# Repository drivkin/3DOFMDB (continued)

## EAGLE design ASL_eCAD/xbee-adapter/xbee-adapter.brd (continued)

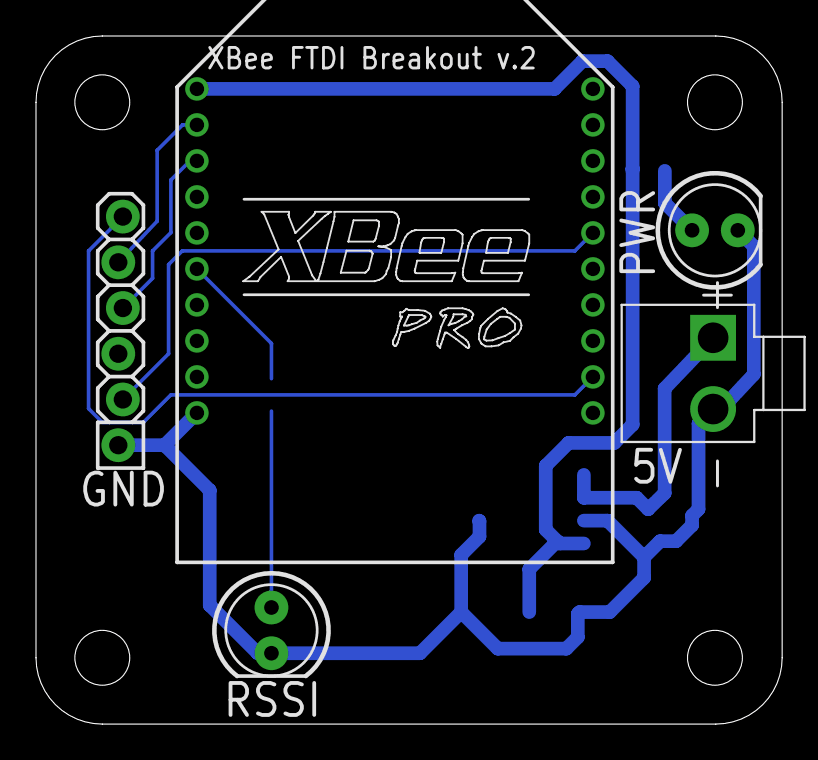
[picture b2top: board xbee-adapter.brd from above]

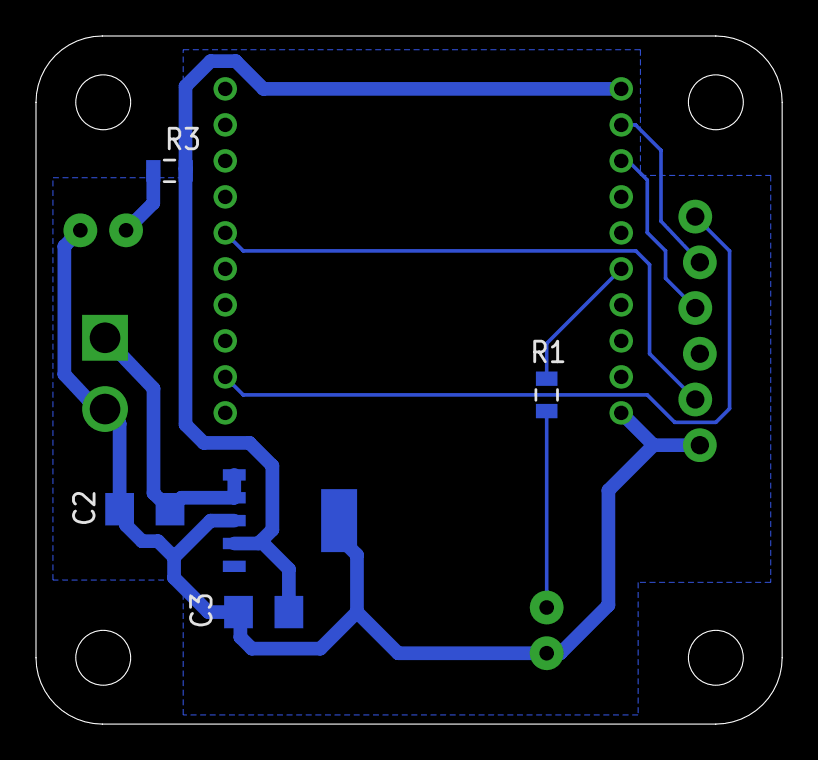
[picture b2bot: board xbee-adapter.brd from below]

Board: 2 copper layers, 41.5 x 38.2 mm, 14 parts (5 on the bottom side), 10 nets.

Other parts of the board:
E$1, E$2, E$3, E$4: STAND-OFF-TIGHT

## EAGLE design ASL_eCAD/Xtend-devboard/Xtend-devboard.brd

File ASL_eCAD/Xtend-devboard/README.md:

# Xtend-devboard

## Description

This board provides a TTL-leve UART connection the Xtend09 wireless modem. The 6-pin header is pinned-out for a standard FTDI cable. This board does not connect power and relies on external power, 2.7-5.5V for the Xtend09.

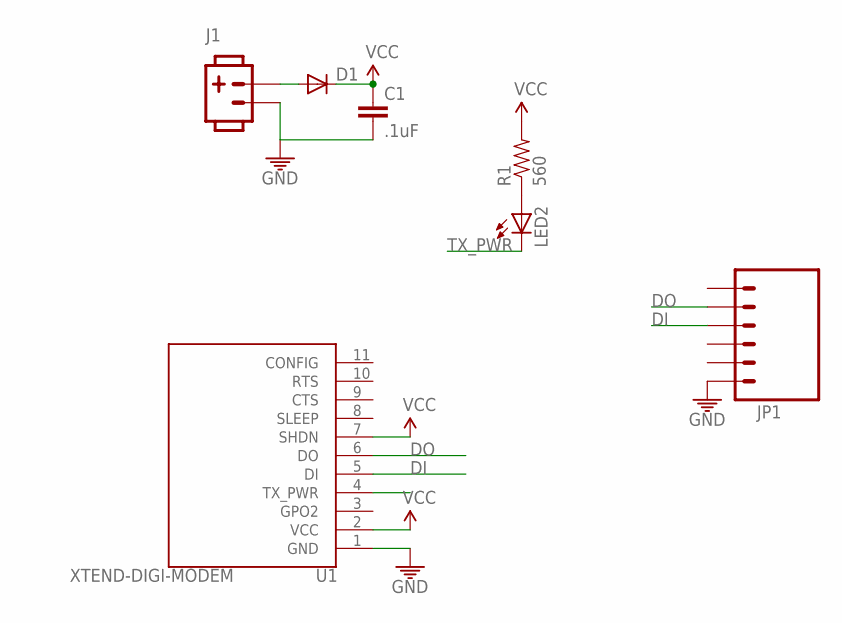
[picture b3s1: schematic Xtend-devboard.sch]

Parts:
C1: .1uF; CAP-PTH-5MM
D1: DIODE1N4148; DIODE-1N4148
J1: POW_CONNECTMALE; SOCKET-MALE-3.96MM-2
JP1: M06LOCK; 1X06_LOCK
LED2: LED5MM
R1: 560; AXIAL-0.3
U1: XTEND-DIGI-MODEM

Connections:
DI: JP1.4, U1.5 (DI)
DO: JP1.5, U1.6 (DO)
GND: C1.2, J1.P$2 (2), JP1.1, U1.1 (GND)
unnamed: D1.A, J1.P$1 (1)
unnamed: LED2.A, R1.P$1 (1)
TX_PWR: LED2.K (C), U1.4 (TX_PWR)
VCC: C1.1, D1.C, R1.P$2 (2), U1.2 (VCC), U1.7 (SHDN)

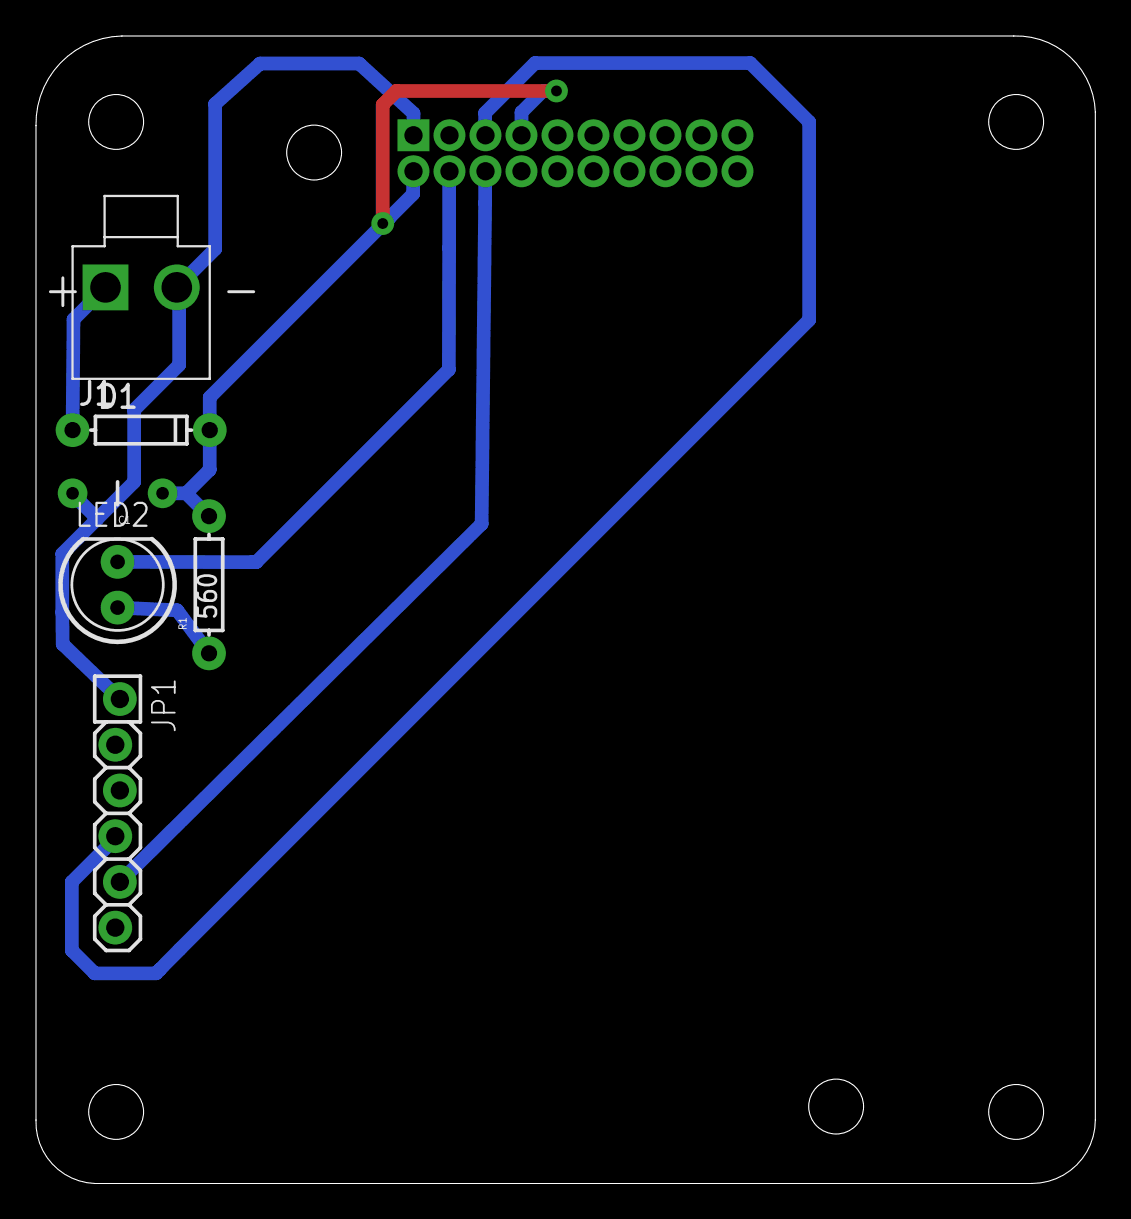
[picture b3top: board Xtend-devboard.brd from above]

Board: 2 copper layers, 58.9 x 63.7 mm, 13 parts (1 on the bottom side), 7 nets.

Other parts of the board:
U$2, U$3, U$4, U$5, U$6, U$7: STAND-OFF-TIGHT

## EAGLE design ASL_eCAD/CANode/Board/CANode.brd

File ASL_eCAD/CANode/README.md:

# CAN Node

## Version
3.0

## Purpose

This is a small development platform built around the dsPIC33F-series of processors by Microchip as a replacement for the Explorer16 development board to be used in the field. With its PICtail extension boards installed, the Explorer16 board is quite large and has sketchy connections to these boards while under motion.

This replacement board was designed to be small, easy to manufacture on a board router, and be easily extensible via Shields ala Arduino platform (though with a different layout).

With the primary design goals of tolerating 24V input, having a CAN transceiver onboard, and being easily extensible and manufactorable, 

 * Tolerate 24V input voltage
 * Have CAN onboard
 * Include at least one status LED
 * Be extensible

## Features
 * 8-36V input
 * Small size (<50mm x <50mm)
 * Onboard CAN transceiver w/ optional grounding & 120ohm terminating resistor
 * 2 user LEDs: amber and red
 * 1% analog temperature sensor (provided by TC1047)
 * 1% analog input voltage sensor (voltage divider)
 * FTDI-cable header for debugging output via UART (TX & RX only)
 * PICkit-compatible ICSP header for programming & debugging
 * Reset button
 * .1" spacing between shield headers allowing perfboard prototyping for shields
 * Efficient switching regulator providing 1.5A at 5V with an LDO capable of 1A at 3.3V
 * Compatibility with all 28-pin PIC24H/dsPIC33E/dsPIC33F processors by Microchip
  * requires PGED at pin 14 and PGEC at pin 15

## Caveats/Notes

This board was designed for manufactoring that is capable of plated vias, so this board may not be possible to manufacture using a board router.

The CANode is a little under 50mm x 50mm, offering a very small amount of space for shields unless they want to exceed the board dimensions. This is one of the primary drawbacks of this board.

Additionally the PGC/PGD pin pairs have a 3.3kOhm resistor inline on those connections. This is to allow the programmer or debugger to operate while the shield is still connected. This does, however, render the internal weak pull-up resistors in the microcontroller useless for active-low, open-drain inputs. When the input is low, the pull-ups are about 90kOhm and the inline resistor is about 3.3kOhm creating a voltage divider that leave a high voltage on the pin.

If a 5V or 3.3V part is being decided between, using a 5V part will improve efficiency. The operating efficiency of the PTN78000 switching regulator increases as load increases, while the efficiency of the 3.3V LDO decreases as the load increases. Therefore it is suggested that parts be 5V where possible.

Programming and debugging is done through PGE3 on the dsPIC33F & PIC24H and through PGE2 on the dsPIC33E. The 3.3V from the programmer is connected to the 3.3V line of the board, so that the programmer can program the processor without it having a separate power source. This may not always work depending on the power draw of the specific processor, but has been shown to work with a dsPIC33FJ128MC802 and Microchip's PICkit3 programmer.

The CAN connector is a standard .1" header. It follows the pinout: 1 - CAN_HI, 2 - CAN_LO, 3 - GND. Pin 3 is unconnected by default with SJ2 providing a solder jumper to connect it to ground. Additionally SJ1 provides a solder-jumper connection for a 120Ohm terminating resistor across CAN_HI and CAN_LO, as they're a differential pair. Standard RC servo cables are a good choice for this connection, even having a black wire on the end for the GND pin facilitating orientation. A silkscreen label for GND is on the board to assist with orientation.

The UART connection is designed to connect to a TTL-level FTDI USB cable (TTL-232R-3V3) using the standard pinout (as seen on the cable side): 1 - GND, 4 - TX, 5 - RX. A silkscreen label for GND is on the board to assist with orientation.

## Designing shields

Shields will likely come in 2 primary designs, one small and one large. The small board will merely use the board area between the two headers. The larger design will extend upwards from the headers to the two top mounting holes, which can be used to support the shield via standoffs.

For the small board design, an orientation indicator should be added in the south-east corner. The indicator on the CANode board is at 1.67x0.25 and the shield's indicator should align with this. The headers have been oriented so that a power-ground short won't occur with the provided power pins, but the shield will likely not operate in a rotated position.

The large board may use the mounting holes at the bottom of the board, but it's recommended that it leaves the area between the mounting holes uncovered for usability. Besides this, there are a few other considerations to keep in mind. At the top the power connector hits the shield, so no components can be mounted above it. The capacitor next to it is also quite tall at 8.5mm and should not have components placed above it as well, though through-hole components should be able to fit (do at your own peril).

## Files
This project is an Eagle 6.x project relying on the ASL.lbr component library, which should be in the root directory.

./Board: Contains the Eagle project for the board.
./Code: Contains testcode in the form of a Simulink model (relies on both the ECAN_dspic project and Lubin's PIC blockset)
./Shields: Contains some general-use example shields for use with this board.

## Partslist

CANode board
  Qty Value                    Device               Partnames             Manufacturer ID                     Price (qty of 10, USD, Digikey)
  1   >=2A,>=40V               DIODE-SCHOTTKY240A   D1                    B240A-13-F                          0.38
  1   green                    LED1206              LED3                  LG N971-KN-1 (green)                0.09
  1   amber                    LED1206              LED2                  APT3216YC (amber)                   0.149
  1   red                      LED1206              LED1                  LH N974-KN-1 (red)                  0.09
  1   straight,.1"             M03LOCK              JP3                   68000-436HLF                        0.641
  1   right-angle,.1"          M06LOCK              JP2                   68016-436HLF                        1.015
  1   straight,.1"             M06LOCK              JP1                   68000-436HLF                        0.641
  1                            TAC_SWITCHPTH        S1                    B3F-1020                            0.393
  3   .1uF                     CAP1206              C7, C9, C10           C1206C104K5RACTU                    0.072
  1   1uF, >3.3V               CAP1206              C6                    CC1206KKX7R7BB105                   0.111
  1   2N7002P                  2N7002P              U6                    2N7002P,215                         0.127
  1   2k, 1%                   RESISTOR0805-RES     R9                    ERJ-6ENF2001V                       0.1
  4   4.7uF, >5V               CAP1206              C1, C2, C3, C5        UMK316AB7475KL-T                    0.19
  2   10k                      RESISTOR0805-RES     R5, R10               ERJ-6GEYJ103V                       0.1
  2   3.3k                     RESISTOR0805-RES     R11, R12              ERJ-6GEYJ332V                       0.1
  1   10uF, >3.3V              CAP1206              C8                    C3216Y5V1A106Z/0.85                 0.124
  2   21k, 1%                  RESISTOR0805-RES     R1, R7                ERJ-6ENF2102V                       0.1
  1   120                      RESISTOR0805-RES     R6                    ERJ-6GEYJ121V                       0.1
  1   100uF, >5V, <11mm height CAP_POL              C4                    10ZLG100MEFC6.3X7, UVR1E101MED      0.208,0.154
  3   330                      RESISTOR0805-RES     R2, R3, R8            ERJ-6GEYJ331V                       0.1
  1   470                      RESISTOR0805-RES     R4                    ERJ-6GEYJ471V                       0.1
  1   DSPIC33FJ128MC802-I/SO   DSPIC33FJ802MC-28    U2                    DSPIC33FJ128MC802-I/SO              5.26
  2   female                   M14DUALROW           J1, J3                PPTC072LFBN-RC                      0.959
  1   MCP1826T-3302E/DC        MCP1826              U3                    MCP1826T-3302E/DC                   0.68
  1   MCP2551-I/SN             MCP2551              U1                    MCP2551-I/SN                        1.02
  1   POW_CONNECTMALE-RA       POW_CONNECTMALE-RA   J2                    0026605020                          0.259
  1   PTN78000W                PTN78000THROUGH-HOLE U4                    PTN78000WAH                         13.5
  4   fm/fm, 1/4", 4-40, 3/8"  standoffs                                  Keystone Electronics 2202           0.402
  4   4-40, 1/4", philips      screws                                     PMS 440 0025 PH                     0.0298 (x100)
  1   TC1047                   TC1047               U5                    TC1047AVNBTR                        0.62

CANode Shield
  Qty Value                    Device               Partnames             Manufacturer ID
  2   male                     M14DUALROW                                 67996-114HLF                        0.703

Connectors
  Qty Value                    Device               Partnames             Manufacturer ID
  1   2-pos, female            POW_CONNECT                                09-48-3025                          0.425

Total cost: ~$32

## Board Assembly
There are two methods for populating the board, either by soldering individual components or by doing the entire top at once through a reflow process.

### Individual Soldering
If you are soldering by hand follow the following steps to populate the board. After every step check connections with a DMM.
 1. Add the power connector and reverse polarity diode.
 2. Add the 5V switching regulator and related components.
   * Power the board up and confirm stable 5V operation.
 3. Add the 3.3V regulator and related components.
   * Power the board up and confirm stable 3.3V operation.
 4. Solder on the reset button circuitry.
   * Use a DMM to check the lines are default high and pulled low when the button is pressed.
 5. Add the PIC processor and ICSP header.
   * Power it on and connect to a PC and attempt to program.
 6. Finish adding the rest of the onboard components doing all through-hole parts last.
 7. Run example code provided in this repository and confirm that it works as expected.

### Batch Soldering
 1. Use a skillet or reflow oven to solder down all SMDs on the top layer.
 2. Solder down the 5V switching regulator, output capacitor, and power connector.
 3. Test the board powering up with both 5V and 3.3V power.
 4. Solder down the reset circuitry and the ICSP header.
   * Confirm operation by attempting to program the PIC.
 5. Finish adding all through-hole parts on the top layer and confirm operation using provided test code.

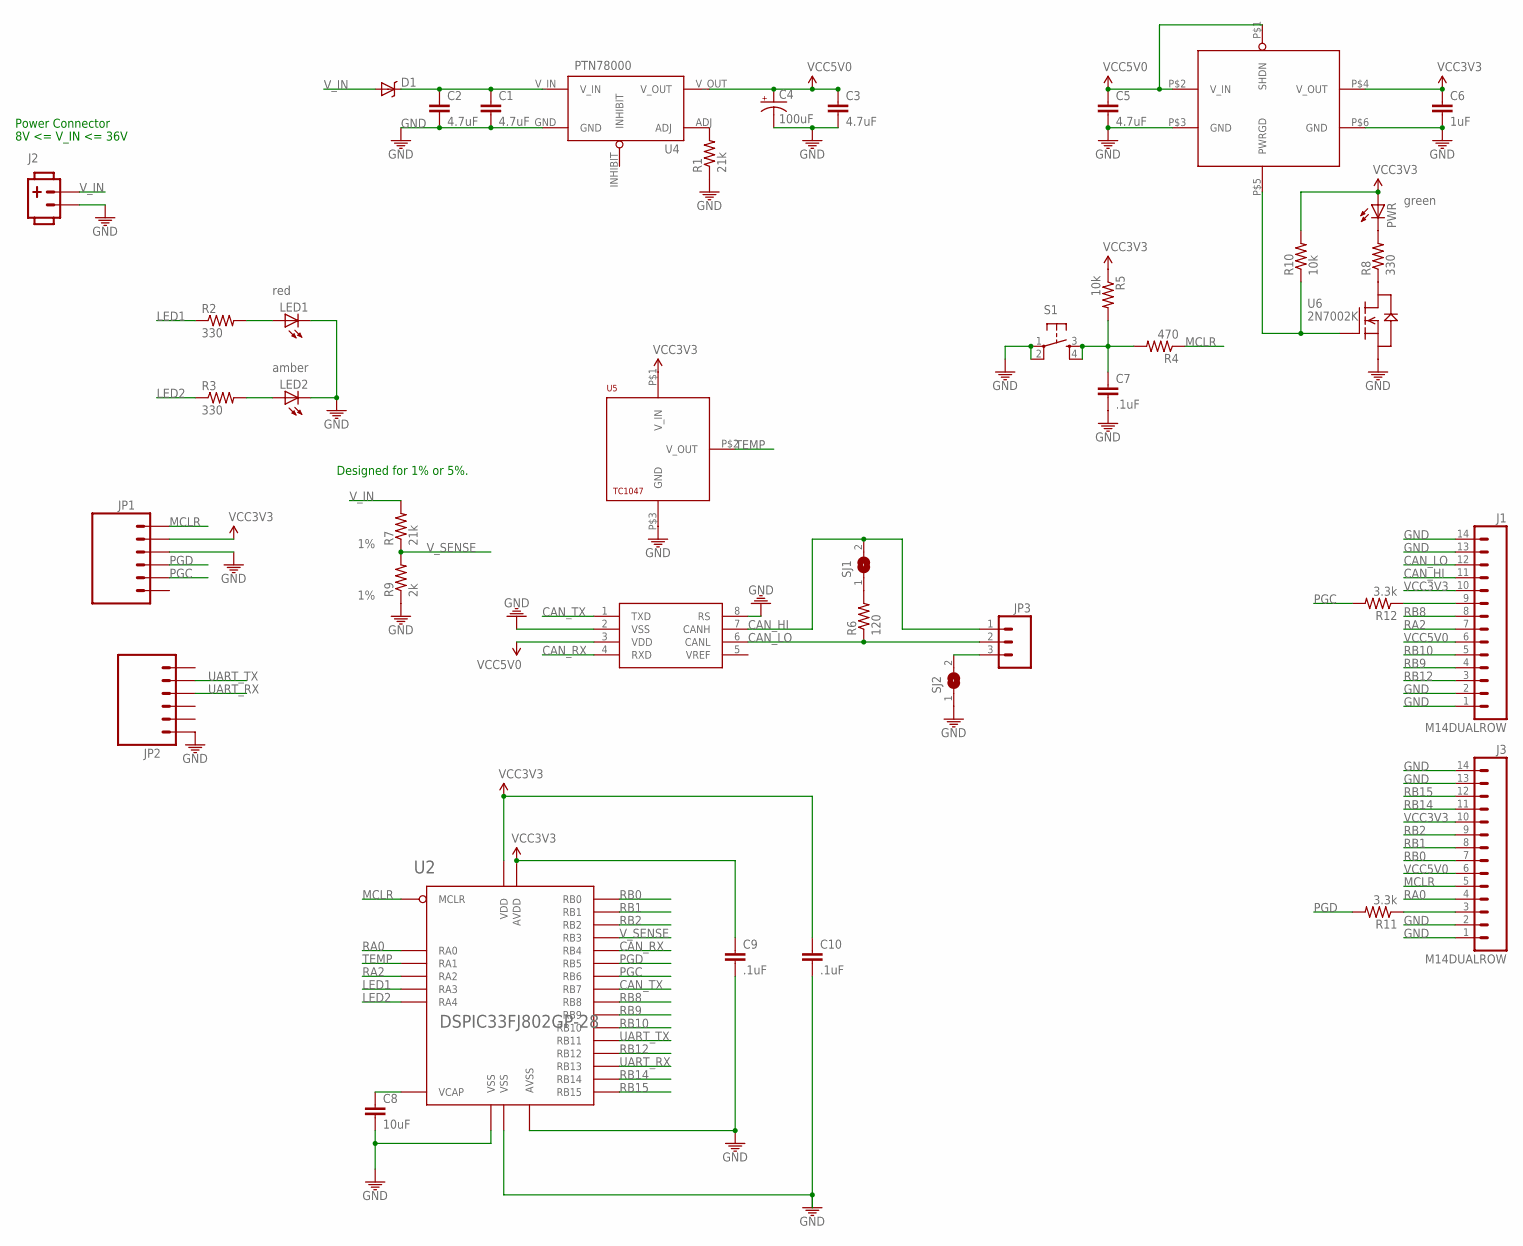
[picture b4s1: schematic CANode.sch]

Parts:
C1, C2, C3, C5: 4.7uF; 1206
C4: 100uF; CPOL-RADIAL-100UF-25V
C6: 1uF; 1206
C7, C9, C10: .1uF; 1206
C8: 10uF; 1206
D1: DIODE-SCHOTTKY240A; SMA-DIODE-B240A
J1, J3: M14DUALROW; 2X7
J2: POW_CONNECTMALE-RA; SOCKET-MALE_RA-3.96MM-2
JP1: M06RA_LOCK; MOLEX-1X6-RA_LOCK
JP2: M06LOCK; 1X06_LOCK
JP3: M03LOCK; 1X03_LOCK
LED1, LED2: LED1206; LED-1206
PWR: LED1206; LED-1206
R1, R7: 21k; 0805
R2, R3, R8: 330; 0805
R4: 470; 0805
R5, R10: 10k; 0805
R6: 120; 0805
R9: 2k; 0805
R11, R12: 3.3k; 0805
S1: TAC_SWITCHPTH; B3F-1020
SJ1, SJ2: SJ
U1: MCP2551; SO08
U2: DSPIC33FJ802GP-28; SOIC28-W
U3: MCP1826; SOT223-5
U4: PTN78000
U5: TC1047; SOT-23B
U6: 2N7002K; SOT23-3

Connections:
CAN_HI: J1.11, JP3.1, SJ1.2, U1.7 (CANH)
CAN_LO: J1.12, JP3.2, R6.1, U1.6 (CANL)
CAN_RX: U1.4 (RXD), U2.P$11 (RB4)
CAN_TX: U1.1 (TXD), U2.P$16 (RB7)
GND: C1.2, C2.2, C3.2, C4.2 (-), C5.2, C6.2, C7.2, C8.2, C9.2, C10.2, J1.1, J1.2, J1.13, J1.14, J2.2, J3.1, J3.2, J3.13, J3.14, JP1.3, JP2.1, LED1.C, LED2.C, R1.1, R9.1, S1.1, S1.2, SJ2.1, U1.2 (VSS), U1.8 (RS), U2.P$8 (VSS), U2.P$19 (VSS), U2.P$27 (AVSS), U3.P$3 (GND), U3.P$6 (GND), U4.GND, U5.P$3 (GND), U6.2 (S)
LED1: R2.1, U2.P$10 (RA3)
LED2: R3.1, U2.P$12 (RA4)
MCLR: J3.5, JP1.1, R4.1, U2.P$1 (MCLR)
unnamed: LED1.A, R2.2
unnamed: R1.2, U4.ADJ
unnamed: LED2.A, R3.2
unnamed: R8.1, U6.3 (D)
unnamed: C1.1, C2.1, D1.C, U4.V_IN
unnamed: C7.1, R4.2, R5.2, S1.3, S1.4
unnamed: C8.1, U2.P$20 (VCAP)
unnamed: PWR.C, R8.2
unnamed: R10.1, U3.P$5 (PWRGD), U6.1 (G)
unnamed: R6.2, SJ1.1
unnamed: J3.3, R11.1
unnamed: JP3.3, SJ2.2
unnamed: J1.9, R12.1
PGC: JP1.5, R12.2, U2.P$15 (RB6)
PGD: JP1.4, R11.2, U2.P$14 (RB5)
RA0: J3.4, U2.P$2 (RA0)
RA2: J1.7, U2.P$9 (RA2)
RB0: J3.7, U2.P$4 (RB0)
RB1: J3.8, U2.P$5 (RB1)
RB2: J3.9, U2.P$6 (RB2)
RB8: J1.8, U2.P$17 (RB8)
RB9: J1.4, U2.P$18 (RB9)
RB10: J1.5, U2.P$21 (RB10)
RB12: J1.3, U2.P$23 (RB12)
RB14: J3.11, U2.P$25 (RB14)
RB15: J3.12, U2.P$26 (RB15)
TEMP: U2.P$3 (RA1), U5.P$2 (V_OUT)
UART_RX: JP2.4, U2.P$24 (RB13)
UART_TX: JP2.5, U2.P$22 (RB11)
VCC3V3: C6.1, C9.1, C10.1, J1.10, J3.10, JP1.2, PWR.A, R5.1, R10.2, U2.P$13 (VDD), U2.P$28 (AVDD), U3.P$4 (V_OUT), U5.P$1 (V_IN)
VCC5V0: C3.1, C4.1 (+), C5.1, J1.6, J3.6, U1.3 (VDD), U3.P$1 (SHDN), U3.P$2 (V_IN), U4.V_OUT
V_IN: D1.A, J2.1, R7.2
V_SENSE: R7.1, R9.2, U2.P$7 (RB3)

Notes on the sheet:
Power Connector
8V <= V_IN <= 36V
Designed for 1% or 5%.

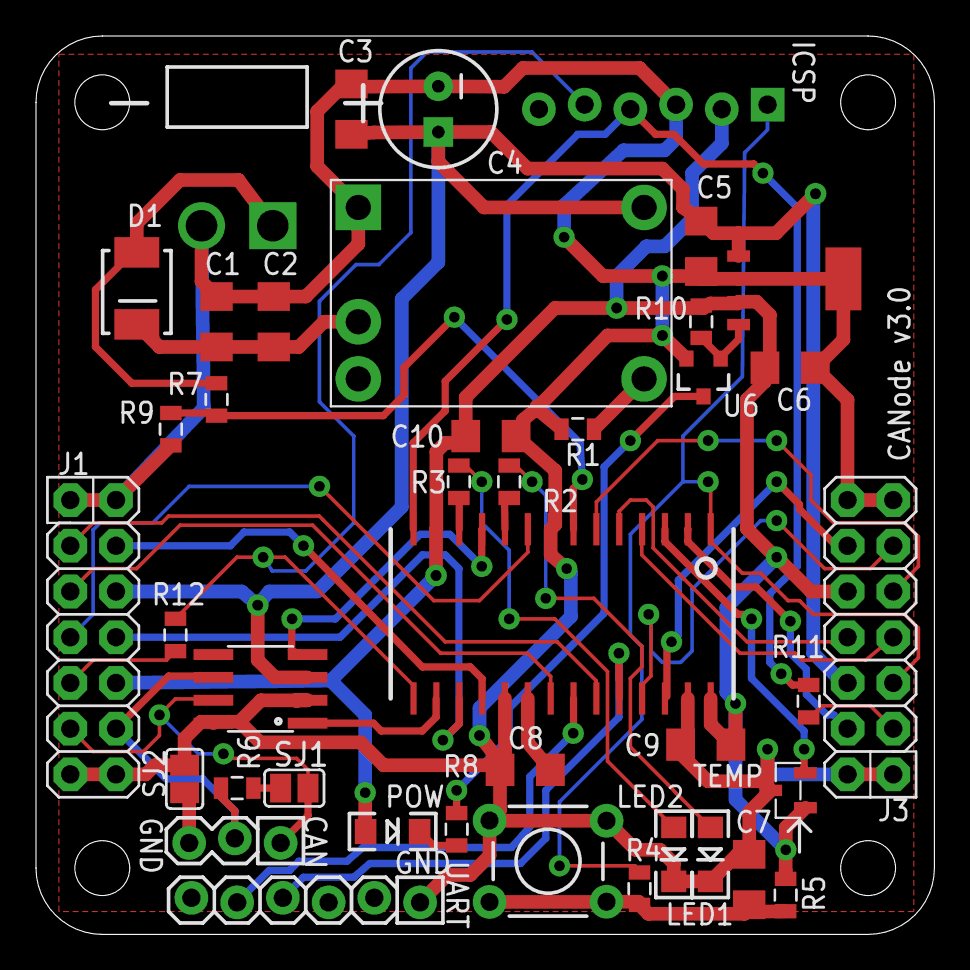
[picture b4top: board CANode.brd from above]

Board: 2 copper layers, 49.9 x 49.9 mm, 45 parts (1 on the bottom side), 41 nets.

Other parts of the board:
JP4, JP5, JP6, JP7: STAND-OFFTIGHT; STAND-OFF-TIGHT

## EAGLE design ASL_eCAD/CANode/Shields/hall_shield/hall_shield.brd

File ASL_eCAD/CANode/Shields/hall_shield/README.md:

# Hall shield

This shield is a breakout board for the AS5048A Hall rotary encoder manufactored by AMS.
This version is designed for the CAN_Node v2 and will not work in earlier versions.

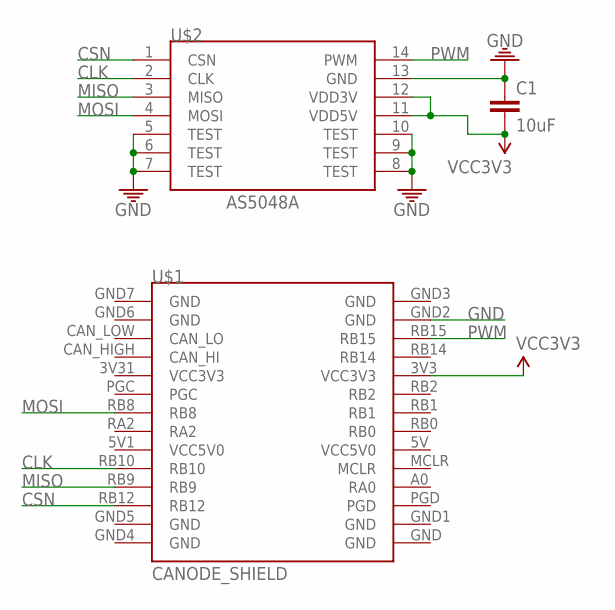
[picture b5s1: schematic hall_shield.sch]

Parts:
C1: 10uF; 1206
U$1: CANODE_SHIELD
U$2: AS5048A; TSSOP14

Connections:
CLK: U$1.RB10, U$2.2 (CLK)
CSN: U$1.RB12, U$2.1 (CSN)
GND: C1.1, U$1.GND2 (GND), U$2.5 (TEST), U$2.6 (TEST), U$2.7 (TEST), U$2.8 (TEST), U$2.9 (TEST), U$2.10 (TEST), U$2.13 (GND)
MISO: U$1.RB9, U$2.3 (MISO)
MOSI: U$1.RB8, U$2.4 (MOSI)
PWM: U$1.RB15, U$2.14 (PWM)
VCC3V3: C1.2, U$1.3V3 (VCC3V3), U$2.11 (VDD5V), U$2.12 (VDD3V)

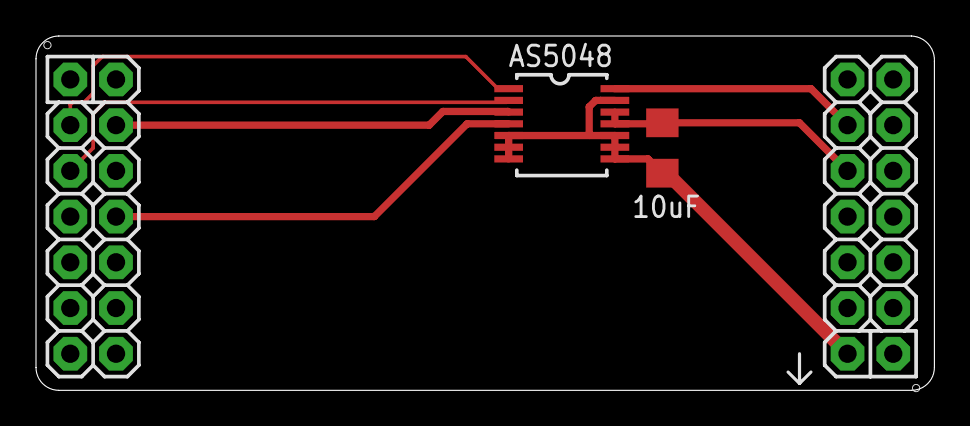
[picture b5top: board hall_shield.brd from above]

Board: 2 copper layers, 49.9 x 19.7 mm, 3 parts (0 on the bottom side), 7 nets.

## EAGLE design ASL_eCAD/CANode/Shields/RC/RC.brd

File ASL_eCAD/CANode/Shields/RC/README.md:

RC Shield for the CAN node.
This board was designed for a Spektrum RC receiver (such as the AR6100e) to plug directly into it to interface with the PIC on the CAN node. While there are only 4 hardware Input Capture peripherals onboard the PIC, that can be done in software as well, so that all 6 channels can be used.

Additionally a jumper header is available to allow for binding transmitters.

Also the reason that all traces use vias to switch sides is so that this board can be manufactored on a board router.

The only parts necessary for this are:
 * 2x 2x7 .1" male headers
 * 1x 3x7 .1" female header OR 7x 1x3 .1" headers 
 * 1x 1x2 .1" male header (and 2-pin jumper)

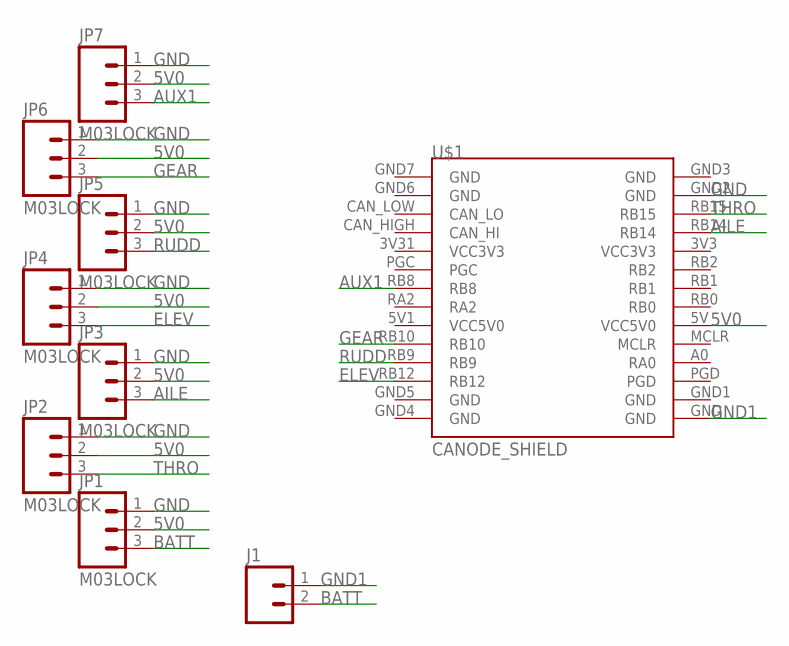
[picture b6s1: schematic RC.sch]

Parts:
J1: M02LOCK; 1X02_LOCK
JP1, JP2, JP3, JP4, JP5, JP6, JP7: M03LOCK; 1X03_LOCK
U$1: CANODE_SHIELD

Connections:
5V0: JP1.2, JP2.2, JP3.2, JP4.2, JP5.2, JP6.2, JP7.2, U$1.5V (VCC5V0)
AILE: JP3.3, U$1.RB14
AUX1: JP7.3, U$1.RB8
BATT: J1.2 (1), JP1.3
ELEV: JP4.3, U$1.RB12
GEAR: JP6.3, U$1.RB10
GND: JP1.1, JP2.1, JP3.1, JP4.1, JP5.1, JP6.1, JP7.1, U$1.GND2 (GND)
GND1: J1.1 (2), U$1.GND
RUDD: JP5.3, U$1.RB9
THRO: JP2.3, U$1.RB15

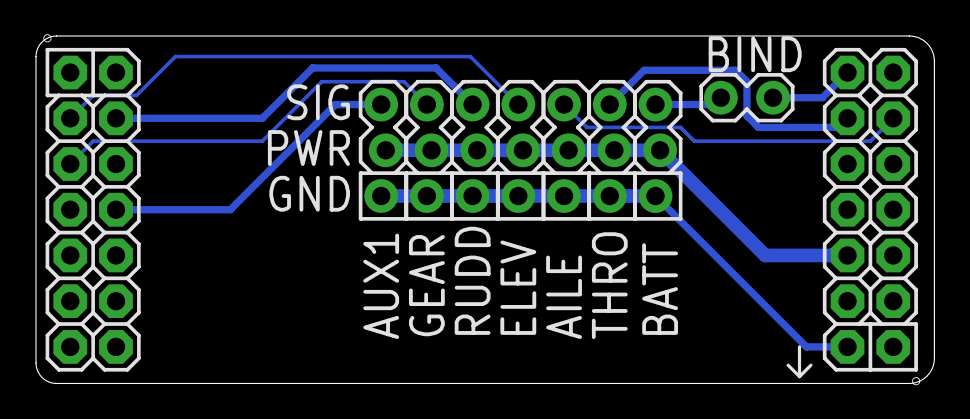
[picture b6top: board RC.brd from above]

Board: 2 copper layers, 49.9 x 19.3 mm, 9 parts (0 on the bottom side), 10 nets.

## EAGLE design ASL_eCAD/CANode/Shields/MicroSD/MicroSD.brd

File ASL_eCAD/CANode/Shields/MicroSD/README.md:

This is a shield for integrating a microSD card with the CAN node board. Relies on 3.3V power. It has also been designed to be make by a board router. Given the pinout below, only SPI2 can be used.

Pinout:
 * DO  -> RB1
 * SCK -> RB14
 * DI  -> RB15
 * CS  -> RB0

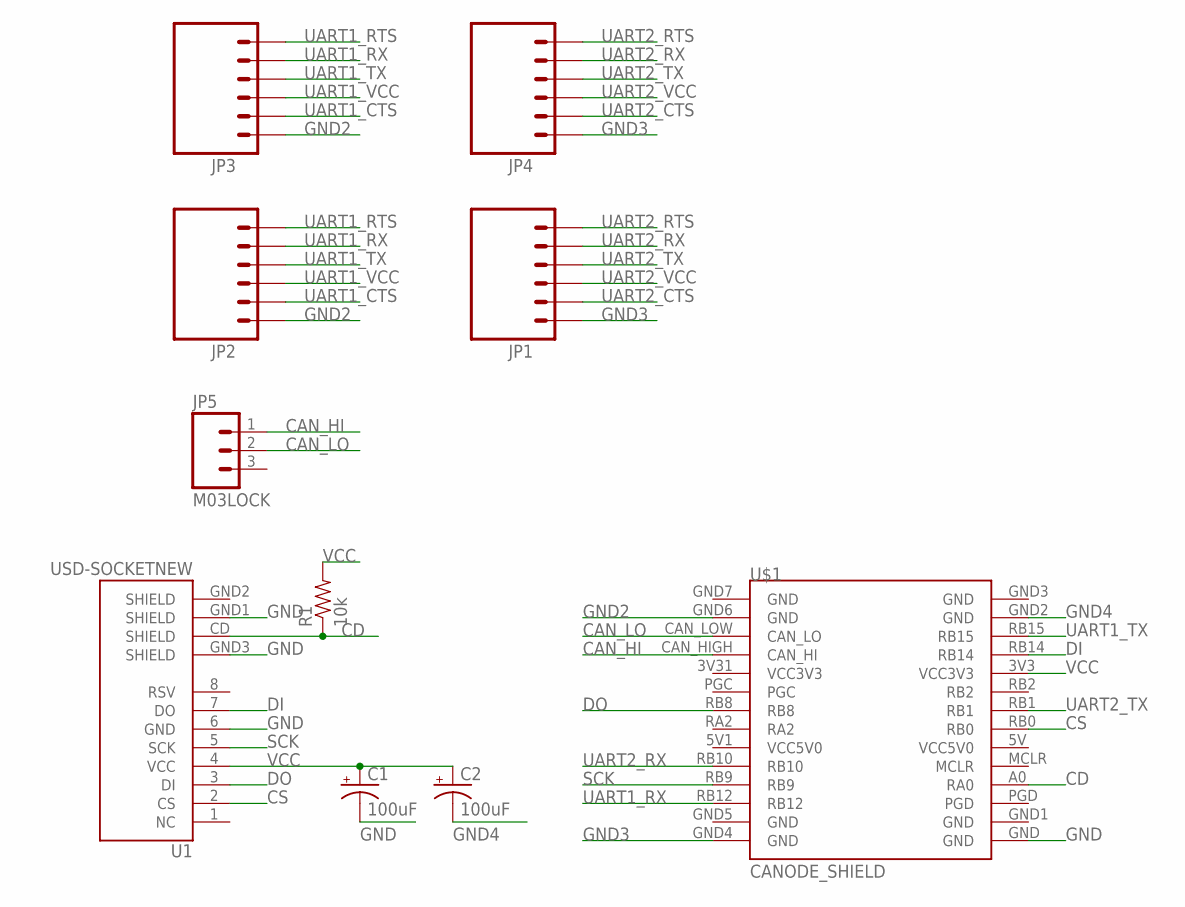
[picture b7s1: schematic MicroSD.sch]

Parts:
C1, C2: 100uF; CPOL-RADIAL-100UF-25V
JP1, JP2, JP3, JP4: M06LOCK; 1X06_LOCK
JP5: M03LOCK; 1X03_LOCK
R1: 10k; 0805
U1: USD-SOCKETNEW; MICRO-SD-SOCKET-PP
U$1: CANODE_SHIELD

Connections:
CAN_HI: JP5.1, U$1.CAN_HIGH (CAN_HI)
CAN_LO: JP5.2, U$1.CAN_LOW (CAN_LO)
CD: R1.1, U1.CD (SHIELD), U$1.A0 (RA0)
CS: U1.2 (CS), U$1.RB0
DI: U1.7 (DO), U$1.RB14
DO: U1.3 (DI), U$1.RB8
GND: C1.2 (-), U1.6 (GND), U1.GND1 (SHIELD), U1.GND3 (SHIELD), U$1.GND
GND2: JP2.1, JP3.1, U$1.GND6 (GND)
GND3: JP1.1, JP4.1, U$1.GND4 (GND)
GND4: C2.2 (-), U$1.GND2 (GND)
SCK: U1.5 (SCK), U$1.RB9
UART1_CTS: JP2.2, JP3.2
UART1_RTS: JP2.6, JP3.6
UART1_RX: JP2.5, JP3.5, U$1.RB12
UART1_TX: JP2.4, JP3.4, U$1.RB15
UART1_VCC: JP2.3, JP3.3
UART2_CTS: JP1.2, JP4.2
UART2_RTS: JP1.6, JP4.6
UART2_RX: JP1.5, JP4.5, U$1.RB10
UART2_TX: JP1.4, JP4.4, U$1.RB1
UART2_VCC: JP1.3, JP4.3
VCC: C1.1 (+), C2.1 (+), R1.2, U1.4 (VCC), U$1.3V3 (VCC3V3)

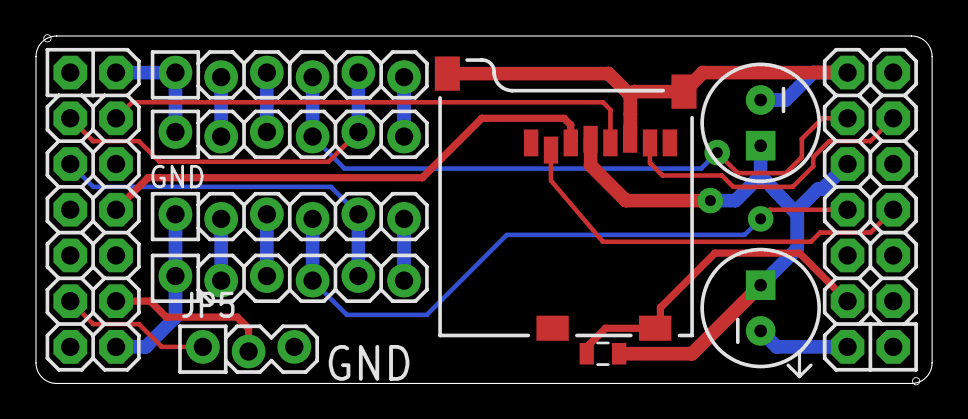
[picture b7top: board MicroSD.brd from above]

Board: 2 copper layers, 49.8 x 19.3 mm, 10 parts (0 on the bottom side), 22 nets.

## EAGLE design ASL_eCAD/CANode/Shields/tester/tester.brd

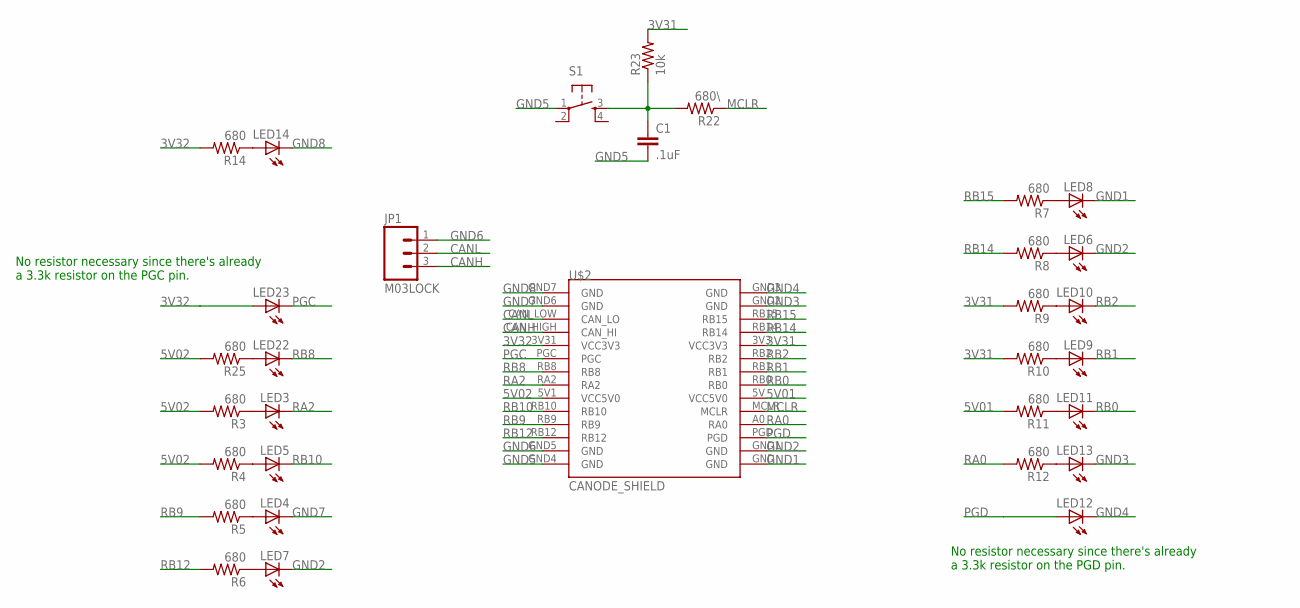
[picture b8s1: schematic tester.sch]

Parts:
C1: .1uF; 1206
JP1: M03LOCK; 1X03_LOCK
LED3, LED4, LED5, LED6, LED7, LED8, LED9, LED10, LED11, LED12, LED13, LED14, LED22, LED23: LED1206; LED-1206
R3, R4, R5, R6, R7, R8, R9, R10, R11, R12, R14, R25: 680; 0805
R22: 680\; 0805
R23: 10k; 0805
S1: TAC_SWITCHPTH; B3F-1020
U$2: CANODE_SHIELD

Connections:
3V31: R9.2, R10.2, R23.2, U$2.3V3 (VCC3V3)
3V32: LED23.A, R14.2, U$2.3V31 (VCC3V3)
5V01: R11.2, U$2.5V (VCC5V0)
5V02: R3.2, R4.2, R25.2, U$2.5V1 (VCC5V0)
CANH: JP1.3, U$2.CAN_HIGH (CAN_HI)
CANL: JP1.2, U$2.CAN_LOW (CAN_LO)
GND1: LED8.C, U$2.GND
GND2: LED6.C, LED7.C, U$2.GND1 (GND)
GND3: LED13.C, U$2.GND2 (GND)
GND4: LED12.C, U$2.GND3 (GND)
GND5: C1.2, S1.1, U$2.GND4 (GND)
GND6: JP1.1, U$2.GND5 (GND)
GND7: LED4.C, U$2.GND6 (GND)
GND8: LED14.C, U$2.GND7 (GND)
MCLR: R22.1, U$2.MCLR
unnamed: C1.1, R22.2, R23.1, S1.3
unnamed: LED22.A, R25.1
unnamed: LED3.A, R3.1
unnamed: LED4.A, R5.1
unnamed: LED5.A, R4.1
unnamed: LED6.A, R8.1
unnamed: LED7.A, R6.1
unnamed: LED8.A, R7.1
unnamed: LED9.A, R10.1
unnamed: LED10.A, R9.1
unnamed: LED11.A, R11.1
unnamed: LED13.A, R12.1
unnamed: LED14.A, R14.1
PGC: LED23.C, U$2.PGC
PGD: LED12.A, U$2.PGD
RA0: R12.2, U$2.A0 (RA0)
RA2: LED3.C, U$2.RA2
RB0: LED11.C, U$2.RB0
RB1: LED9.C, U$2.RB1
RB2: LED10.C, U$2.RB2
RB8: LED22.C, U$2.RB8
RB9: R5.2, U$2.RB9
RB10: LED5.C, U$2.RB10
RB12: R6.2, U$2.RB12
RB14: R8.2, U$2.RB14
RB15: R7.2, U$2.RB15

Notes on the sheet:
No resistor necessary since there's already a 3.3k resistor on the PGD pin.
No resistor necessary since there's already a 3.3k resistor on the PGC pin.

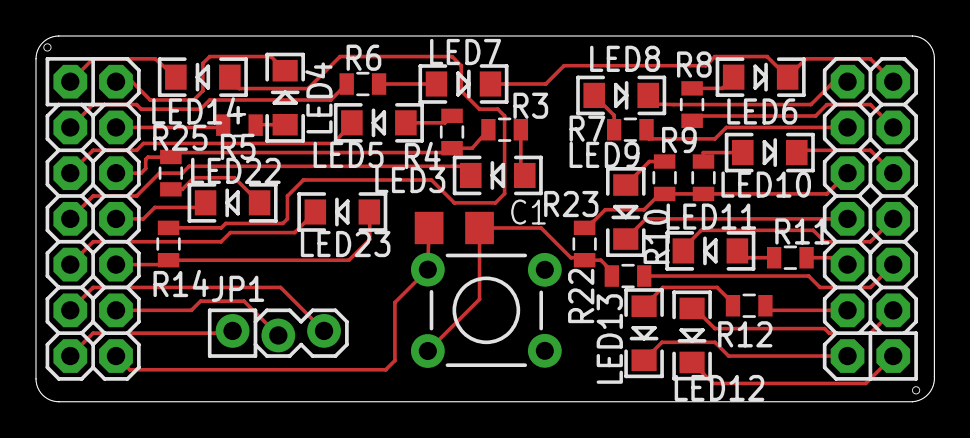
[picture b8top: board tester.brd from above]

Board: 2 copper layers, 49.9 x 20.3 mm, 32 parts (0 on the bottom side), 41 nets.

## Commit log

2015-04-01 :boom::camel: Added .gitattributes & .gitignore files
2015-04-01 First commit
    The three motor drivers are done
2015-04-01 Shrunk it down
    Squeezed the motor driving parts together to get the thing to be an inch
    and a half narrower (now about 3.5 inches wide)
2015-04-03 Almost all components
    Almost everything is down and routed, going to the bathroom
2015-04-03 All components placed and routed
    All components placed and routed, many DRC errors, but mostly to do with
    the vias on the bottom of the DRV. Need to fix those, and make sure to
    put in a bunch of ground plane vias
2015-04-03 Improved
    Minor schematic adjustments (and according routing), and 8844 polygons
    fixed
2015-04-03 Passes DRC
    Now passes DRC
2015-04-13 Names, GND vias, Mounting holes
    Moved the names around so they don't overlap, added a bunch of ground
    vias (not very systematically), and 4 mounting holes in the corners (not
    quite symmetrical)
2015-04-21 Filled out BOM with digikey parts
    Except for what you can sample from microchip and TI
2015-04-21 Added ASL eCAD
    Added ASL eCAD folder (used to be a repo, but no longer)
2015-04-27 Moved the DSPIC33 library into the github repo
    yup, that's it
